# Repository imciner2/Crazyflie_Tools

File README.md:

# Crazyflie_Tools
Miscellaneous tools and projects used to measure parameters about the Crazyflie Nano-Quadcopter.

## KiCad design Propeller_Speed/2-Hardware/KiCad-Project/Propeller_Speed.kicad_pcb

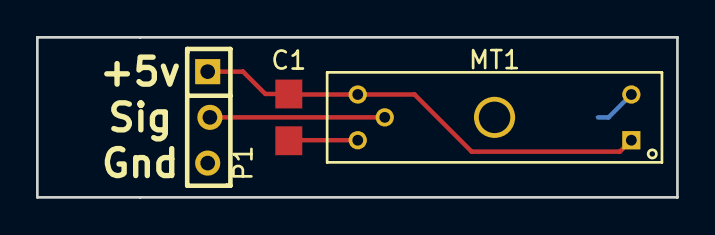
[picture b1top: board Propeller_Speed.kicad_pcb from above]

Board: 2 copper layers, 35.6 x 8.9 mm, 4 parts (1 on the bottom side), 4 nets.

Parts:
C1: 0.1u; SMD_0805
MT1: GP1A57HRJ00F; SHARP_GP1A57HRJ00F
P1: CONN_1x3; CONN_2.54mm_1x3
R1: 470; SMD_0805

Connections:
/GND: C1.2, MT1.5, P1.3, R1.2
/Vcc: C1.1, MT1.1, MT1.3, P1.1
unnamed: MT1.2, R1.1
unnamed: MT1.4, P1.2

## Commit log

2017-01-19 Added Kicad Libraries
2017-01-19 New library version
2017-01-19 Electrical design for speed measurement device
2017-01-19 Initial IDF file, it is missing part locations though
2017-01-19 Schematic of interface board
2017-01-19 Datasheets used by the speed measurement system
2017-01-19 Updated anular ring size to meet design rules
2017-01-19 Remade gerber files
2017-01-19 Updated part outline
2017-01-19 Uploaded currently used trackable frame
2017-01-20 Added physical properties to readme
2017-01-20 Fixing the readme
2017-01-20 Removed temp file
2017-01-20 Initial design for mount to force sensor
2017-02-05 Modified resistor value
2017-02-05 Barebones project
2017-02-05 Reference manual for uC
2017-02-05 Various notes related to the design
2017-02-05 Removed 2 unneeded files
2017-02-08 Reorganized project for new Makefile
2017-02-08 Skeleton code for the timers and counters
2017-02-08 Fixed timer period
2017-02-23 Updated pin map to be correct. Removed averaging
2017-03-03 Moved propeller speed software
2017-03-04 Changed directory structure
2017-03-05 Software for measuring the rise time of the Crazyflie motors
2017-03-05 Randomly changed file
2017-03-08 Streamlined ISR functions
2017-03-08 Made capture time longer
2017-04-15 CAD Renderings
2017-05-16 Fixed library location issue
